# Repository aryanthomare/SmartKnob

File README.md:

<h1 align="center">SmartKnob</h1>

<p align="center">
  A programmable force-feedback knob for your computer. Custom motor-driver PCB, closed-loop haptic firmware,<br>
  a native Windows companion app and a parametric 3D-printed enclosure, all designed in house.
</p>

A brushless gimbal motor sits under the knob. By driving it with the right torque at every angle, the firmware makes
the same physical knob feel like a stepped volume dial, a smooth scroll wheel or a switch with hard end stops, and
changes that feel on the fly as you switch tasks on the PC. The knob talks to a small Windows tray app over USB or
Bluetooth LE, and works on its own as a media volume knob when the app isn't running.

## Contents

- [Features](#features)
- [System overview](#system-overview)
- [Hardware: the driver PCB](#hardware-the-driver-pcb)
- [Firmware](#firmware)
- [Desktop app](#desktop-app)
- [Enclosure](#enclosure)
- [How it was built](#how-it-was-built)
- [Building and flashing](#building-and-flashing)
- [Repository layout](#repository-layout)

## Features

- **Software-defined feel.** Detent strength, steps per degree and spring end stops are pushed from the PC per mode.
- **Exact volume, not key nudges.** With the app running, the knob sets system or per-app volume to the percent, and
  follows changes made elsewhere (keyboard, Windows mixer) so the dial never drifts.
- **Five modes:** system volume, volume of the focused app, scroll, zoom, and left/right arrow keys.
- **Wired or wireless.** USB-C, or Bluetooth LE from the 12 V barrel jack alone. The app switches between them
  automatically and prefers the cable.
- **Works without the app** as a USB or Bluetooth HID volume knob.
- **Liquid Glass style UI** rendered in software by a 280 KB native executable that uses no CPU while idle.

## System overview

```mermaid
flowchart LR
  subgraph Knob["Knob (ESP32-S3 firmware)"]
    ENC["AS5600 encoder<br/>12-bit, I²C"] --> CTRL["Control loop ~4.7 kHz<br/>FOC torque + haptic engine"]
    CTRL --> DRV["DRV8316 3-phase driver<br/>→ gimbal BLDC motor"]
    CTRL <--> PROTO["Line protocol<br/>HELLO · CFG · VAL · PING"]
    CTRL --> HID["HID volume keys<br/>(standalone)"]
  end
  PROTO <-- "USB CDC serial" --> APP
  PROTO <-- "BLE Nordic UART" --> APP
  HID -- "USB HID / HID-over-GATT" --> WIN["Windows"]
  subgraph PC["Windows PC"]
    APP["SmartKnob.exe<br/>tray app"] --> CA["Core Audio<br/>system + per-app volume"]
    APP --> SI["SendInput<br/>scroll · zoom · arrows"]
  end
```

The haptics always run on the knob, so the feel never waits on the PC. The app only sends a *haptic config* (range,
degrees per step, detent strength, wall stiffness) when the mode changes, and receives value changes back.

## Hardware: the driver PCB

A 54 × 54 mm, four-layer board designed in KiCad. The motor's axis sits at the board centre, the AS5600 encoder board
stacks above it on M3 standoffs, and the motor mounts on top of that.

| Block | Part | Notes |
|---|---|---|
| MCU | ESP32-S3-MINI-1-N8 | Native USB (no USB-UART bridge), BLE 5, 8 MB flash |
| Motor driver | TI DRV8316CR | 3-phase, integrated FETs, SPI config, 3× PWM mode, current-sense outputs |
| Encoder | AS5600 breakout | 12-bit magnetic angle over I²C, on its own board under the motor |
| Motor | 34.5 mm gimbal BLDC | 7 pole pairs (measured during bring-up) |
| 12 V input | DC barrel jack | P-MOSFET reverse-polarity block, 15 V gate clamp, SMAJ16A TVS |
| 5 V | TI TPS54202 buck | 12 V → 5.08 V, diode-ORed with USB VBUS |
| 3.3 V | AP2112K LDO | MCU, encoder and breakout header |
| USB-C | HRO TYPE-C-31-M-12 | 500 mA polyfuse, USBLC6 ESD protection |
| Misc | | JST-PH motor and encoder connectors, 2×5 breakout header, BOOT/RESET buttons, VM voltage sense |

```mermaid
flowchart LR
  J1["12 V barrel"] --> Q1["Reverse-polarity<br/>P-MOSFET + TVS"] --> VM["+12 V (VM)"]
  VM --> DRV["DRV8316<br/>motor supply"]
  VM --> BUCK["TPS54202 buck<br/>→ 5.08 V"] --> D4["Schottky"] --> V5["+5 V"]
  USB["USB-C VBUS"] --> F1["Polyfuse"] --> D3["Schottky"] --> V5
  V5 --> LDO["AP2112K"] --> V33["+3.3 V<br/>MCU · encoder"]
  VM --> SENSE["÷11 divider → GPIO7<br/>(VM sense)"]
```

The two 5 V sources are diode-ORed, so the logic runs from either USB or the barrel jack. Motor power only comes
from the barrel jack, so on USB alone the knob still reads the encoder and talks to the PC, and the firmware turns
haptics off until 12 V is present.

**Layer stack.** Signals on the outer layers, a solid ground plane on inner 1 under everything, and inner 2 split
between the 12 V motor supply and 3.3 V. The DRV8316's thermal pad drops straight into the ground plane through a via
array, and the ESP32 antenna overhangs a copper keep-out.

<details>
<summary><b>Schematic sheets</b> (hierarchical: power, driver, MCU, connectors)</summary>

The design notes on each sheet record the datasheet decisions: feedback divider values, which DRV8316 pins may not
float, strapping pins to avoid, ADC1-only analog inputs because ADC2 is unusable with the radio on, and so on.

**Power**

**Motor driver**

**MCU**

**Connectors**

Full PDF: [hardware/smartknob_driver/smartknob_driver_schematic.pdf](hardware/smartknob_driver/smartknob_driver_schematic.pdf)
</details>

**Fabrication.** [`hardware/smartknob_driver/fab`](hardware/smartknob_driver/fab) has Gerbers, drill files and a
JLCPCB assembly BOM and placement file with LCSC part numbers, so the board can be ordered fully assembled.

## Firmware

[`volume_knob/src/main.cpp`](volume_knob/src/main.cpp) · Arduino on ESP32-S3 via PlatformIO

**Motor control.** At power-up the firmware calibrates itself: it aligns the rotor with a fixed voltage vector to find
the encoder direction and the electrical zero, then applies a test push to learn the torque sign. After that it runs
voltage-mode field-oriented control: every loop it reads the encoder over 400 kHz I²C, computes the electrical angle,
and puts the requested torque on the q-axis through 20 kHz PWM. The loop runs at about 4.7 kHz. Drive voltage is
capped per supply (3 V on 12 V, 1.2 V when VM is low), and a DRV8316 fault or loss of motor power drops the knob
into plain-encoder mode instead of driving blind.

**Haptic engine.** The knob tracks an integer value in `[lo, hi]` with one value every `step` degrees. Around each
value a capped spring pulls the knob to the detent centre, and past either end a stiffer spring wall pushes it back,
with damping on both. Hysteresis on the step boundary stops the value chattering.

<p align="center">
  <picture>
    <source media="(prefers-color-scheme: dark)" srcset="docs/images/haptic_profile_dark.png">
    
  </picture>
</p>

**Two ways to run.**

- *Host mode:* the app sends a haptic config per mode and the knob streams value changes back.
- *Standalone:* with no app for 3 s, the knob becomes a media-key volume knob. HID can only nudge the volume, so on
  connect it drives Windows to 0 % and back up to a known level, unless the app reported the real level shortly before
  it went away.

**Protocol.** Plain text lines, identical over USB serial and Bluetooth:

| Direction | Message | Meaning |
|---|---|---|
| PC → knob | `HELLO` | Handshake, answered with `INFO name=SmartKnob fw=2 hap=<0/1>` |
| PC → knob | `CFG lo= hi= val= step= det= wall=` | Range, current value, degrees per step, detent volts, wall stiffness |
| PC → knob | `VAL v=` | Move the value without moving the knob (volume changed elsewhere) |
| PC → knob | `PING vol=` | Keep-alive (3 s timeout) plus the PC's real volume, answered with `PONG hap= vm=` |
| knob → PC | `VAL v=` | The user turned the knob |

**Connectivity.** USB enumerates as a composite device (HID consumer control + CDC serial) with its own product ID.
Over Bluetooth LE the knob exposes two services on one connection: HID-over-GATT for the standalone volume keys and
the Nordic UART Service for the protocol. Every message the firmware prints goes to both transports.

## Desktop app

[`desktop/smartknob.cpp`](desktop/smartknob.cpp) · C++17, Win32, GDI+, C++/WinRT

<table>
  <tr>
    <td></td>
    <td></td>
  </tr>
  <tr>
    <td colspan="2" align="center"><br><sub>Volume popup shown while turning</sub></td>
  </tr>
</table>

A tray app with a floating panel for picking the mode and click strength, and a volume popup that appears while you
turn the knob.

- **Volume:** sets the Windows master volume exactly through Core Audio (`IAudioEndpointVolume`), and listens for
  changes made elsewhere so the knob's haptic position stays in sync. It tags its own writes so it can ignore them.
- **App volume:** follows the foreground window (`SetWinEventHook`) and adjusts every audio session of that process.
- **Scroll / Zoom / Arrow keys:** relative modes that emit wheel events, Ctrl+wheel or ←/→ through `SendInput`, each
  with its own detent feel.
- **Connection:** finds the knob by USB ID and opens it with overlapped I/O on a reader thread. If there's no cable it
  connects to the paired knob's GATT service with C++/WinRT on a worker thread, and moves to USB as soon as a cable
  appears. The UI thread never blocks on either.

**Liquid Glass material, in software.** The panel and popup follow Apple's Liquid Glass guidelines without any GPU
framework:

- The screen behind the window is captured, downsampled, saturated and box-blurred. The windows exclude themselves from
  capture, so they never see their own pixels.
- Each pixel then gets a lens offset from the shape's signed distance field, so content bends at the rim, with slight
  chromatic dispersion, a specular rim lit from the top left, an adaptive tint and a soft shadow.
- The small popup flips light or dark with the luminance behind it, and corners are concentric (inner radius = outer
  radius − padding).
- It honours Windows dark mode, transparency effects, animation settings and high contrast.
- It only re-captures while a window is visible, and only re-renders when what's behind it changed: about 1 % of
  one core with the panel open, nothing when hidden.

**Footprint:** one 280 KB statically linked executable, no runtime to install, about 7 MB of memory, 0 % CPU idle.
Settings live in `%APPDATA%\SmartKnob\settings.ini`.

## Enclosure

[`enclosure/smartknob_enclosure.fs`](enclosure/smartknob_enclosure.fs) · Onshape FeatureScript

The whole enclosure is a single code-defined Onshape feature, so changing a standoff height or the knob fit is one
constant and a rebuild.

- **Cover:** one printed piece. A side profile (flat deck over the motor, rounded slope down to a low nose on the
  cable side) is intersected with the plan shape, filleted along the top and shelled from the open bottom. It has
  cut-outs for the motor, barrel jack, USB-C plug and paper-clip access to BOOT/RESET.
- **Base plate:** a locating lip, and counterbored M3 holes on the board's 24 mm mounting square.
- **Encoder spacers:** printed rings that lift the AS5600 board clear of the barrel jack.
- **Knob cap:** 40 mm, 40 grip flutes and a pointer dimple. Four pegs press-fit into the rotor's M2.5 holes, with peg
  diameter as a printer-tuning constant.
- **Reference stack:** the populated PCB (built from the KiCad 3D models' bounding boxes, in the same coordinate frame
  as the KiCad STEP export), the encoder board, standoffs and motor.
- **Self-checks:** the feature measures the distance between the enclosure and everything inside it, warns on
  interference and reports the minimum clearance.

## How it was built

The whole stack was designed in house and brought up one layer at a time.

1. **Board design.** A hierarchical schematic in KiCad with datasheet decisions written onto each sheet, then a
   four-layer layout around a centred motor axis, with the JST connectors on the cable side and the power entry on
   the opposite edge. Exported Gerbers, drill files and a JLCPCB assembly BOM and placement file.
2. **Encoder bring-up.** [`encoder_test`](encoder_test/src/main.cpp) scans the I²C bus and streams raw angle,
   magnet status and AGC to confirm the magnet height.
3. **Motor bring-up.** [`motor_test`](motor_test/src/main.cpp) brings up the DRV8316 over SPI and checks supply and
   faults. It steps through the phases while watching the rotor, sweeps electrical revolutions to measure the pole
   pairs (7), and spins the motor open-loop in both directions before any closed-loop code runs.
4. **Enclosure.** Iterated in Onshape around a STEP export of the real board. Parameters live as constants rather
   than feature-dialog inputs, so pushing new code never invalidates the feature.
5. **Firmware.** Closed-loop FOC and the generic haptic engine, first as a standalone USB volume knob, then with the
   host protocol.
6. **Desktop app.** First prototyped in Python, then rewritten as a native Win32 executable to keep the memory and
   CPU footprint negligible.
7. **Bluetooth.** Added as a second transport carrying the same protocol, so the knob runs from the barrel jack alone.

**Problems found on real hardware**

- **Port mix-up.** The knob first enumerated with Espressif's default USB product ID, the same one as the chip's
  built-in flashing port, which the app deliberately never opens. The firmware now sets its own PID. Because the
  Arduino core starts USB before `setup()` when CDC-on-boot is enabled, that meant turning CDC-on-boot off and owning
  the serial object.
- **Buzzing at the end stops.** After the knob was released past 0 % or 100 %, the wall spring returned it to rest
  about 1° past the end, where friction holds it. There the wall's damping term was amplifying one-LSB encoder
  jitter, which differentiates to tens of degrees per second, into ±0.25 V of noise. That was three times the spring
  force, so the motor sat buzzing between −0.32 V and +0.17 V. A heavier velocity filter plus a 30 °/s deadband on
  the damping fixed it: the motor now holds a steady −0.07 V. A test command that shifts the knob's reference point
  made the bug reproducible on the bench without touching the knob.

## Building and flashing

**Firmware** (PlatformIO):

```sh
cd volume_knob
pio run -t upload        # first flash goes through the chip's USB-Serial/JTAG port (COM3 in platformio.ini)
```

Once the firmware is running, the board shows up as `303A:4B4E` (HID + serial) and the flashing port disappears. To
reflash, choose **Disconnect for firmware update** in the app's tray menu, then open the knob's COM port at 1200 baud
to reboot into the bootloader. Holding BOOT while plugging in also works.

**Desktop app** (Visual Studio with the C++ workload):

```bat
desktop\build.bat
desktop\SmartKnob.exe
```

`SmartKnob.exe --snapshot <dir>` renders the panel and popup over the current screen to PNGs and exits. The UI images
in this README were made that way.

**Bluetooth:** pair "SmartKnob" once in Windows Settings → Bluetooth. Windows caches the knob's services, so after
changing them in firmware, remove the device and pair again.

## Repository layout

```
hardware/smartknob_driver/   KiCad project: schematic, 4-layer PCB, custom symbols/footprints, fab outputs
volume_knob/                 Main firmware: FOC, haptic engine, USB + BLE protocol, HID
encoder_test/                Bring-up: AS5600 over I²C
motor_test/                  Bring-up: DRV8316 + open-loop motor tests
desktop/                     Windows companion app (single C++ file + build script)
enclosure/                   Onshape FeatureScript enclosure + board STEP export
docs/images/                 README images (renders, schematic sheets, app snapshots)
```

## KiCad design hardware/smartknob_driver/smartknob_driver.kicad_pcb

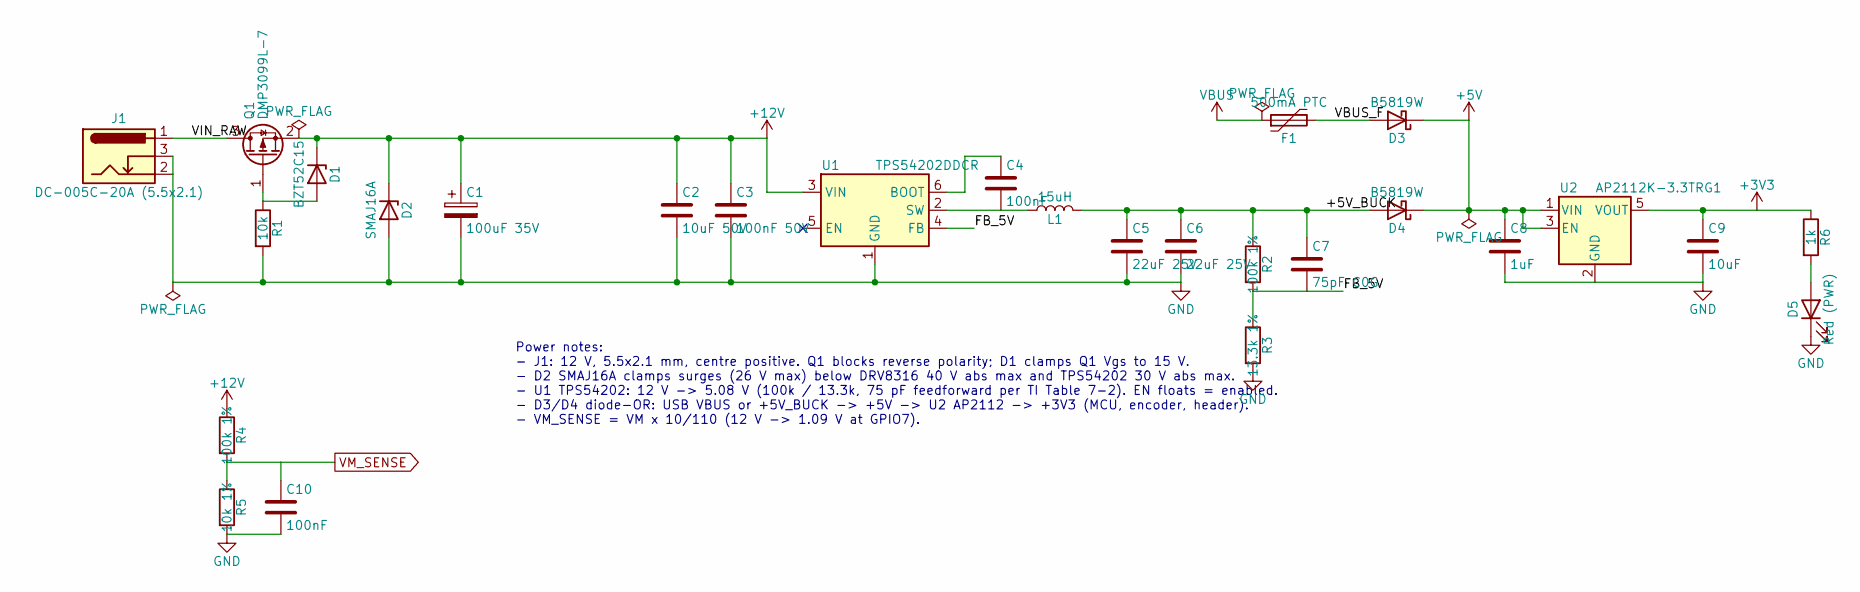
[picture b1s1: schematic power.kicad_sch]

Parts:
C1: 100uF 35V; CP_Elec_6.3x7.7; LCSC C294520
C2: 10uF 50V; C_1206_3216Metric; LCSC C13585
C3: 100nF 50V; C_0603_1608Metric; LCSC C14663
C4, C10: 100nF; C_0402_1005Metric; LCSC C1525
C5, C6: 22uF 25V; C_0805_2012Metric; LCSC C45783
C7: 75pF C0G; C_0402_1005Metric; LCSC C107010
C8: 1uF; C_0402_1005Metric; LCSC C52923
C9: 10uF; C_0603_1608Metric; LCSC C19702
D1: BZT52C15; D_SOD-123; LCSC C2932746
D2: SMAJ16A; D_SMA; LCSC C74561
D3, D4: B5819W; D_SOD-123; LCSC C8598
D5: Red (PWR); LED_0603_1608Metric; LCSC C2286
F1: 500mA PTC; Fuse_0805_2012Metric; LCSC C20978
J1: DC-005C-20A (5.5x2.1); BarrelJack_Hroparts_DC-005C-20A_Horizontal; LCSC C84007
L1: 15uH; L_Sunlord_SWPA5040S; LCSC C44888
Q1: DMP3099L-7; SOT-23; LCSC C155244
R1: 10k; R_0402_1005Metric; LCSC C25744
R2, R4: 100k 1%; R_0402_1005Metric; LCSC C25741
R3: 13.3k 1%; R_0402_1005Metric; LCSC C274352
R5: 10k 1%; R_0402_1005Metric; LCSC C25744
R6: 1k; R_0402_1005Metric; LCSC C11702
U1: TPS54202DDCR; SOT-23-6; LCSC C191884
U2: AP2112K-3.3TRG1; SOT-23-5; LCSC C51118

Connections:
+3V3: C9.1, R6.1, U2.5 (VOUT); also elsewhere on the board
+5V: C8.1, D3.1 (K), D4.1 (K), U2.1 (VIN), U2.3 (EN)
+12V: C1.1, C2.1, C3.1, D1.1 (K), D2.1 (K), Q1.2 (S), R4.1, U1.3 (VIN); also elsewhere on the board
/Power/+5V_BUCK: C5.1, C6.1, C7.1, D4.2 (A), L1.2, R2.1
/Power/FB_5V: C7.2, R2.2, R3.1, U1.4 (FB)
/Power/VBUS_F: D3.2 (A), F1.2
/Power/VIN_RAW: J1.1, Q1.3 (D)
GND: C1.2, C2.2, C3.2, C5.2, C6.2, C8.2, C9.2, C10.2, D2.2 (A), D5.1 (K), J1.2, J1.3, R1.2, R3.2, R5.2, U1.1 (GND), U2.2 (GND); also elsewhere on the board
unnamed: D1.2 (A), Q1.1 (G), R1.1
unnamed: D5.2 (A), R6.2
unnamed: C4.1, U1.6 (BOOT)
unnamed: C4.2, L1.1, U1.2 (SW)
VBUS: F1.1; also elsewhere on the board
VM_SENSE: C10.1, R4.2, R5.1; also elsewhere on the board

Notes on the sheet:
Power notes: - J1: 12 V, 5.5x2.1 mm, centre positive. Q1 blocks reverse polarity; D1 clamps Q1 Vgs to 15 V. - D2 SMAJ16A clamps surges (26 V max) below DRV8316 40 V abs max and TPS54202 30 V abs max. - U1 TPS54202: 12 V -> 5.08 V (100k / 13.3k, 75 pF feedforward per TI Table 7-2). EN floats = enabl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

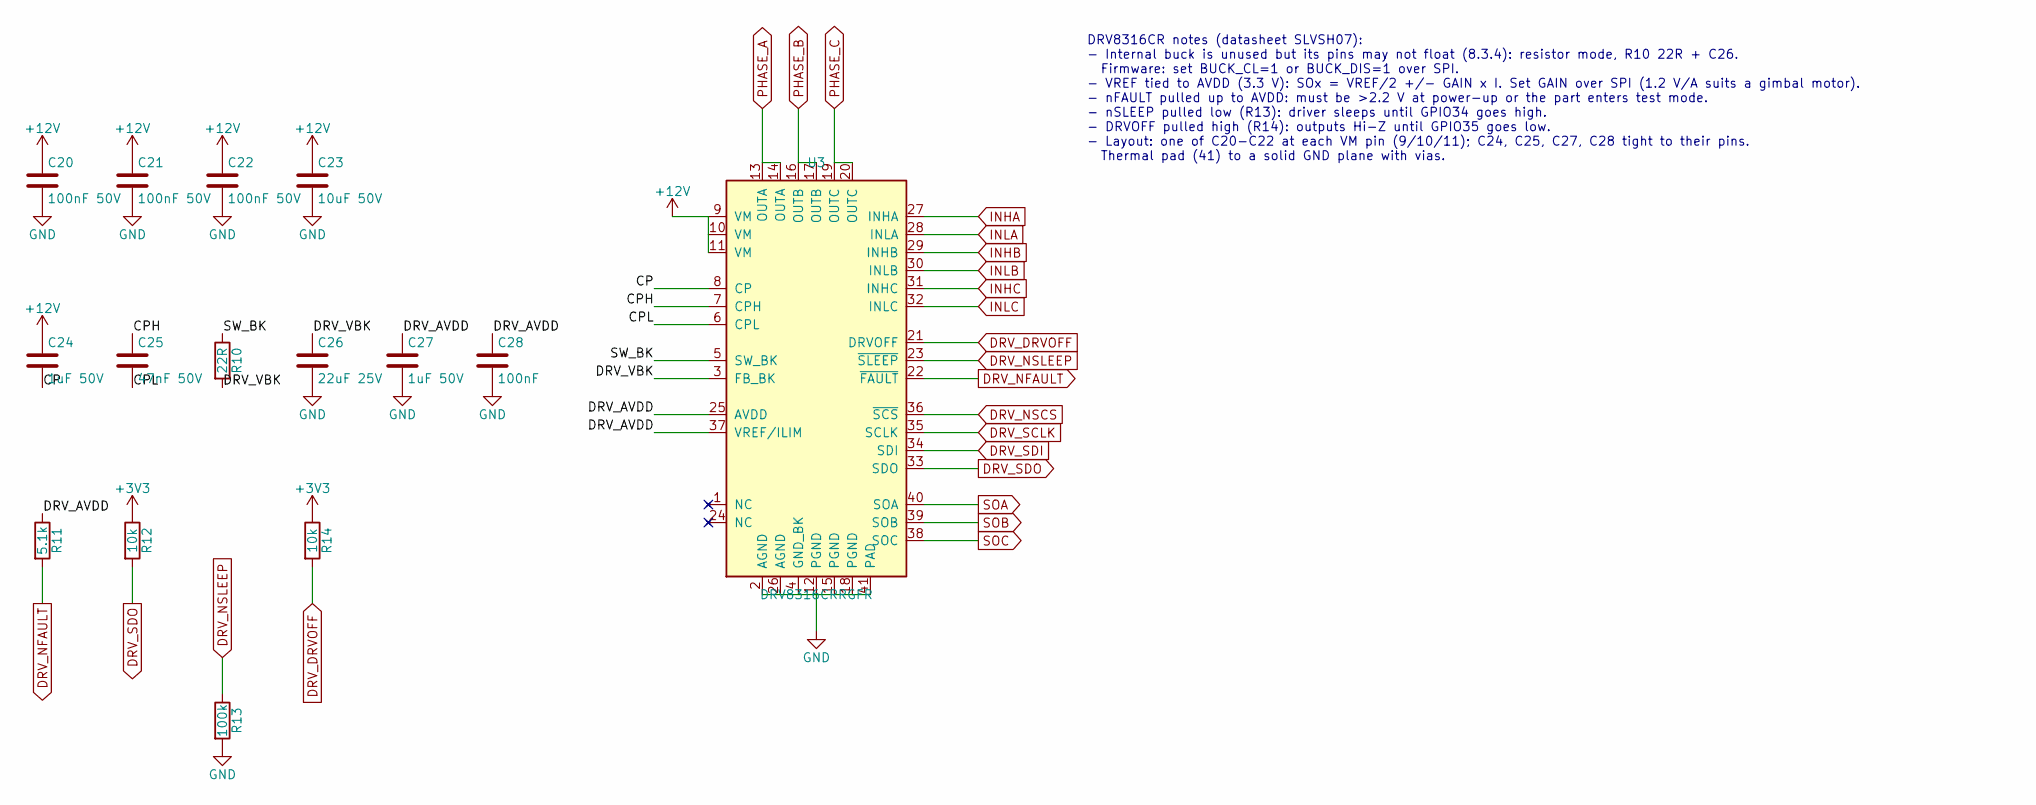
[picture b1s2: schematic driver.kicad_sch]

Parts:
C20, C21, C22: 100nF 50V; C_0603_1608Metric; LCSC C14663
C23: 10uF 50V; C_1206_3216Metric; LCSC C13585
C24, C27: 1uF 50V; C_0603_1608Metric; LCSC C15849
C25: 47nF 50V; C_0603_1608Metric; LCSC C1622
C26: 22uF 25V; C_0805_2012Metric; LCSC C45783
C28: 100nF; C_0402_1005Metric; LCSC C1525
R10: 22R; R_0603_1608Metric; LCSC C23345
R11: 5.1k; R_0402_1005Metric; LCSC C25905
R12, R14: 10k; R_0402_1005Metric; LCSC C25744
R13: 100k; R_0402_1005Metric; LCSC C25741
U3: DRV8316CRRGFR; TI_RGF0040E_VQFN-40-1EP_5x7mm_P0.5mm_EP3.7x5.7mm_ThermalVias; LCSC C5447274

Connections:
+3V3: R12.1, R14.1; also elsewhere on the board
+12V: C20.1, C21.1, C22.1, C23.1, C24.1, U3.9 (VM), U3.10 (VM), U3.11 (VM); also elsewhere on the board
/Driver/CP: C24.2, U3.8 (CP)
/Driver/CPH: C25.1, U3.7 (CPH)
/Driver/CPL: C25.2, U3.6 (CPL)
/Driver/DRV_AVDD: C27.1, C28.1, R11.1, U3.25 (AVDD), U3.37 (VREF/ILIM)
/Driver/DRV_VBK: C26.1, R10.2, U3.3 (FB_BK)
/Driver/SW_BK: R10.1, U3.5 (SW_BK)
DRV_DRVOFF: R14.2, U3.21 (DRVOFF); also elsewhere on the board
DRV_NFAULT: R11.2, U3.22 (~FAULT); also elsewhere on the board
DRV_NSCS: U3.36 (~SCS); also elsewhere on the board
DRV_NSLEEP: R13.1, U3.23 (~SLEEP); also elsewhere on the board
DRV_SCLK: U3.35 (SCLK); also elsewhere on the board
DRV_SDI: U3.34 (SDI); also elsewhere on the board
DRV_SDO: R12.2, U3.33 (SDO); also elsewhere on the board
GND: C20.2, C21.2, C22.2, C23.2, C26.2, C27.2, C28.2, R13.2, U3.2 (AGND), U3.4 (GND_BK), U3.12 (PGND), U3.15 (PGND), U3.18 (PGND), U3.26 (AGND), U3.41 (PAD); also elsewhere on the board
INHA: U3.27 (INHA); also elsewhere on the board
INHB: U3.29 (INHB); also elsewhere on the board
INHC: U3.31 (INHC); also elsewhere on the board
INLA: U3.28 (INLA); also elsewhere on the board
INLB: U3.30 (INLB); also elsewhere on the board
INLC: U3.32 (INLC); also elsewhere on the board
PHASE_A: U3.13 (OUTA), U3.14 (OUTA); also elsewhere on the board
PHASE_B: U3.16 (OUTB), U3.17 (OUTB); also elsewhere on the board
PHASE_C: U3.19 (OUTC), U3.20 (OUTC); also elsewhere on the board
SOA: U3.40 (SOA); also elsewhere on the board
SOB: U3.39 (SOB); also elsewhere on the board
SOC: U3.38 (SOC); also elsewhere on the board

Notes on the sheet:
DRV8316CR notes (datasheet SLVSH07): - Internal buck is unused but its pins may not float (8.3.4): resistor mode, R10 22R + C26. Firmware: set BUCK_CL=1 or BUCK_DIS=1 over SPI. - VREF tied to AVDD (3.3 V): SOx = VREF/2 +/- GAIN x I. Set GAIN over SPI (1.2 V/A suits a gimbal motor). - nFAULT pulled 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

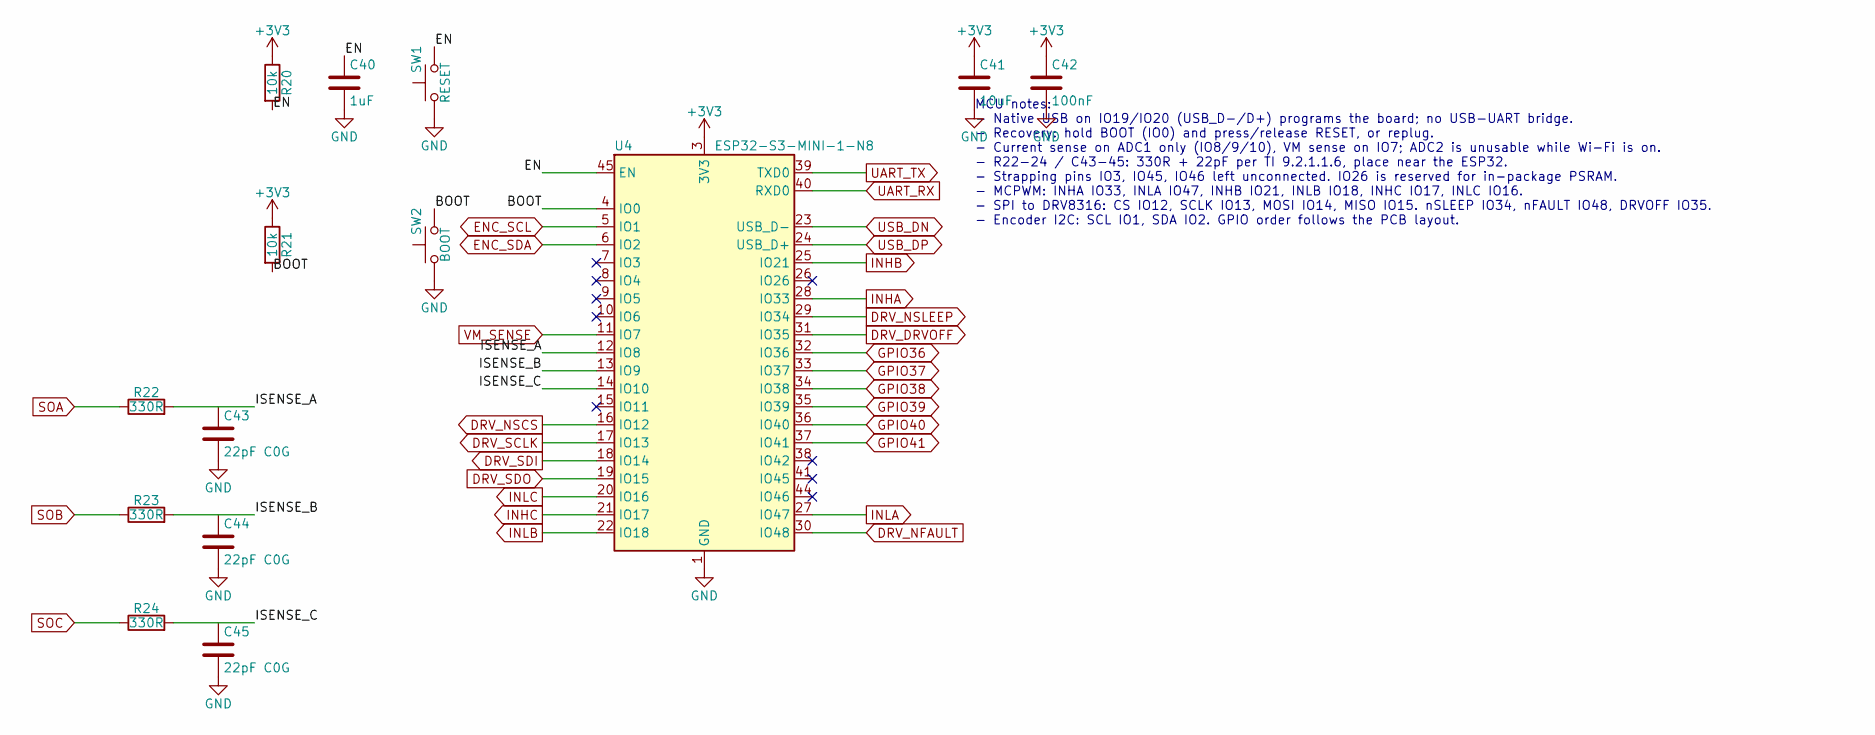
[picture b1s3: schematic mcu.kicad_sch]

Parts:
C40: 1uF; C_0402_1005Metric; LCSC C52923
C41: 10uF; C_0603_1608Metric; LCSC C19702
C42: 100nF; C_0402_1005Metric; LCSC C1525
C43, C44, C45: 22pF C0G; C_0402_1005Metric; LCSC C1555
R20, R21: 10k; R_0402_1005Metric; LCSC C25744
R22, R23, R24: 330R; R_0402_1005Metric; LCSC C25104
SW1: RESET; SW_Push_1P1T_XKB_TS-1187A; LCSC C318884
SW2: BOOT; SW_Push_1P1T_XKB_TS-1187A; LCSC C318884
U4: ESP32-S3-MINI-1-N8; ESP32-S2-MINI-1; LCSC C2913206

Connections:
+3V3: C41.1, C42.1, R20.1, R21.1, U4.3 (3V3); also elsewhere on the board
/MCU/BOOT: R21.2, SW2.2, U4.4 (IO0)
/MCU/EN: C40.1, R20.2, SW1.2, U4.45 (EN)
/MCU/ISENSE_A: C43.1, R22.2, U4.12 (IO8)
/MCU/ISENSE_B: C44.1, R23.2, U4.13 (IO9)
/MCU/ISENSE_C: C45.1, R24.2, U4.14 (IO10)
DRV_DRVOFF: U4.31 (IO35); also elsewhere on the board
DRV_NFAULT: U4.30 (IO48); also elsewhere on the board
DRV_NSCS: U4.16 (IO12); also elsewhere on the board
DRV_NSLEEP: U4.29 (IO34); also elsewhere on the board
DRV_SCLK: U4.17 (IO13); also elsewhere on the board
DRV_SDI: U4.18 (IO14); also elsewhere on the board
DRV_SDO: U4.19 (IO15); also elsewhere on the board
ENC_SCL: U4.5 (IO1); also elsewhere on the board
ENC_SDA: U4.6 (IO2); also elsewhere on the board
GND: C40.2, C41.2, C42.2, C43.2, C44.2, C45.2, SW1.1, SW2.1, U4.1 (GND), U4.2 (GND), U4.42 (GND), U4.43 (GND), U4.46 (GND), U4.47 (GND), U4.48 (GND), U4.49 (GND), U4.50 (GND), U4.51 (GND), U4.52 (GND), U4.53 (GND), U4.54 (GND), U4.55 (GND), U4.56 (GND), U4.57 (GND), U4.58 (GND), U4.59 (GND), U4.60 (GND), U4.61 (GND), U4.62 (GND), U4.63 (GND), U4.64 (GND), U4.65 (GND); also elsewhere on the board
GPIO36: U4.32 (IO36); also elsewhere on the board
GPIO37: U4.33 (IO37); also elsewhere on the board
GPIO38: U4.34 (IO38); also elsewhere on the board
GPIO39: U4.35 (IO39); also elsewhere on the board
GPIO40: U4.36 (IO40); also elsewhere on the board
GPIO41: U4.37 (IO41); also elsewhere on the board
INHA: U4.28 (IO33); also elsewhere on the board
INHB: U4.25 (IO21); also elsewhere on the board
INHC: U4.21 (IO17); also elsewhere on the board
INLA: U4.27 (IO47); also elsewhere on the board
INLB: U4.22 (IO18); also elsewhere on the board
INLC: U4.20 (IO16); also elsewhere on the board
SOA: R22.1; also elsewhere on the board
SOB: R23.1; also elsewhere on the board
SOC: R24.1; also elsewhere on the board
UART_RX: U4.40 (RXD0); also elsewhere on the board
UART_TX: U4.39 (TXD0); also elsewhere on the board
USB_DN: U4.23 (USB_D-); also elsewhere on the board
USB_DP: U4.24 (USB_D+); also elsewhere on the board
VM_SENSE: U4.11 (IO7); also elsewhere on the board

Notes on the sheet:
MCU notes: - Native USB on IO19/IO20 (USB_D-/D+) programs the board; no USB-UART bridge. - Recovery: hold BOOT (IO0) and press/release RESET, or replug. - Current sense on ADC1 only (IO8/9/10), VM sense on IO7; ADC2 is unusable while Wi-Fi is on. - R22-24 / C43-45: 330R + 22pF per TI 9.2.1.1.6, pla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

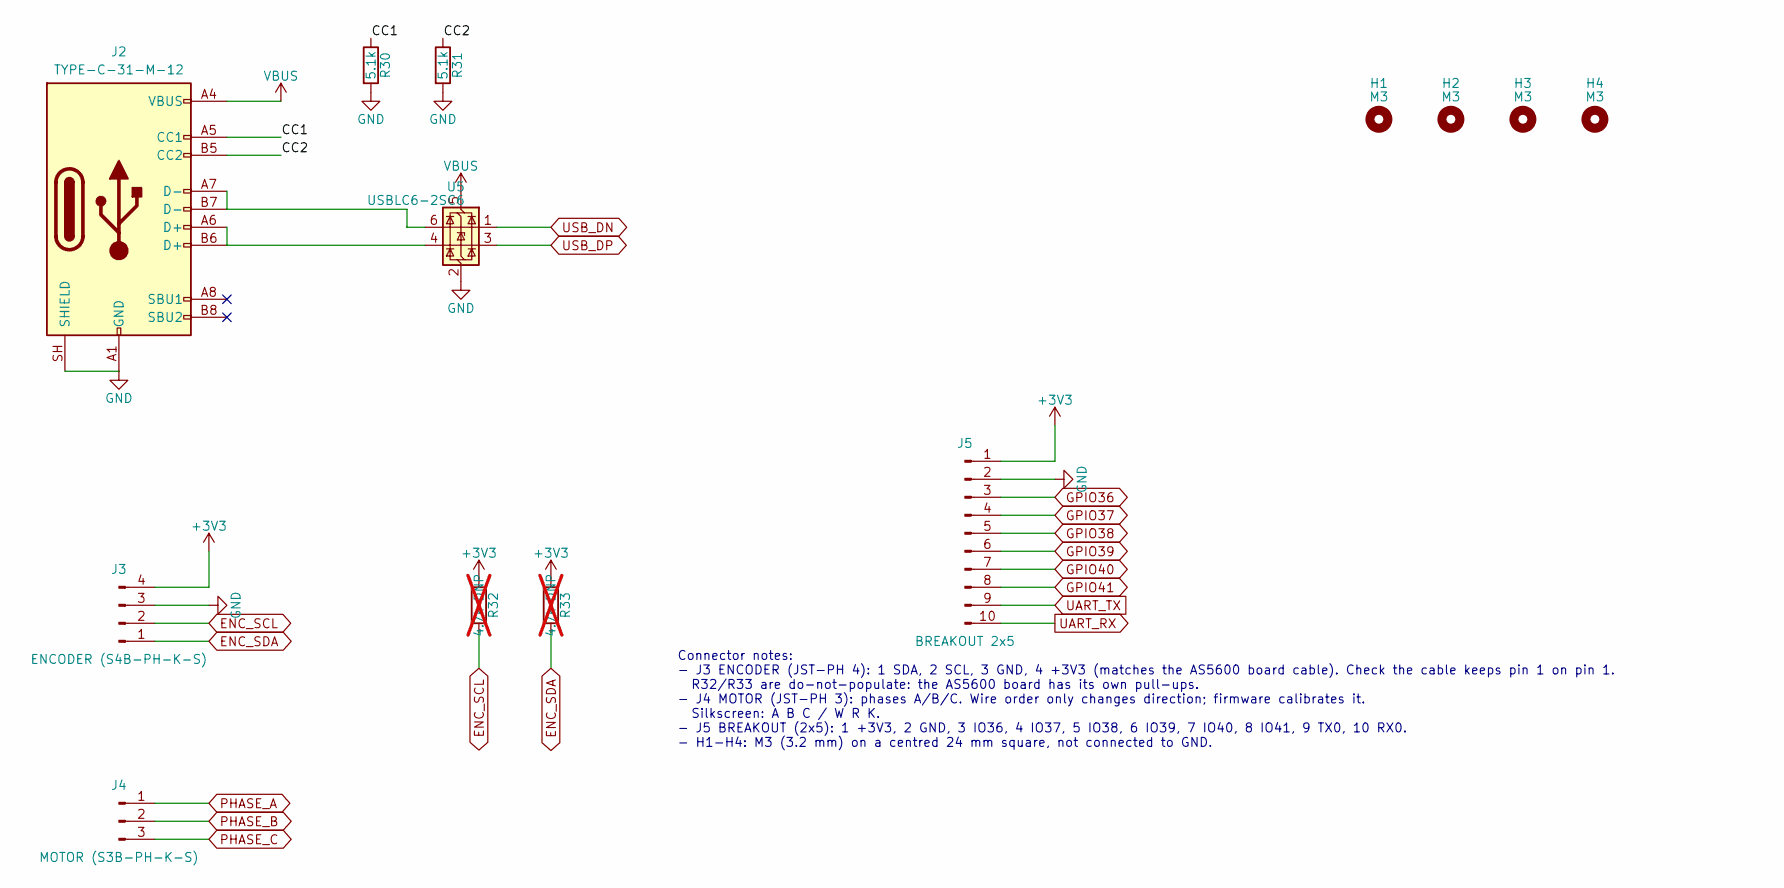
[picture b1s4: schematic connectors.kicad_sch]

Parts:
H1, H2, H3, H4: M3; MountingHole_3.2mm_M3
J2: TYPE-C-31-M-12; USB_C_Receptacle_HRO_TYPE-C-31-M-12; LCSC C165948
J3: ENCODER (S4B-PH-K-S); JST_PH_S4B-PH-K_1x04_P2.00mm_Horizontal; LCSC C157926
J4: MOTOR (S3B-PH-K-S); JST_PH_S3B-PH-K_1x03_P2.00mm_Horizontal; LCSC C157929
J5: BREAKOUT 2x5; PinHeader_2x05_P2.54mm_Vertical
R30, R31: 5.1k; R_0402_1005Metric; LCSC C25905
R32, R33: 4.7k DNP; R_0402_1005Metric; LCSC C25900; not fitted
U5: USBLC6-2SC6; SOT-23-6; LCSC C7519

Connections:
+3V3: J3.4, J5.1, R32.1, R33.1; also elsewhere on the board
/Connectors/CC1: J2.A5 (CC1), R30.1
/Connectors/CC2: J2.B5 (CC2), R31.1
ENC_SCL: J3.2, R32.2; also elsewhere on the board
ENC_SDA: J3.1, R33.2; also elsewhere on the board
GND: J2.A1 (GND), J2.A12 (GND), J2.B1 (GND), J2.B12 (GND), J2.SH (SHIELD), J3.3, J5.2, R30.2, R31.2, U5.2 (GND); also elsewhere on the board
GPIO36: J5.3; also elsewhere on the board
GPIO37: J5.4; also elsewhere on the board
GPIO38: J5.5; also elsewhere on the board
GPIO39: J5.6; also elsewhere on the board
GPIO40: J5.7; also elsewhere on the board
GPIO41: J5.8; also elsewhere on the board
unnamed: J2.A6 (D+), J2.B6 (D+), U5.4 (I/O2)
unnamed: J2.A7 (D-), J2.B7 (D-), U5.6 (I/O1)
PHASE_A: J4.1; also elsewhere on the board
PHASE_B: J4.2; also elsewhere on the board
PHASE_C: J4.3; also elsewhere on the board
UART_RX: J5.10; also elsewhere on the board
UART_TX: J5.9; also elsewhere on the board
USB_DN: U5.1 (I/O1); also elsewhere on the board
USB_DP: U5.3 (I/O2); also elsewhere on the board
VBUS: J2.A4 (VBUS), J2.A9 (VBUS), J2.B4 (VBUS), J2.B9 (VBUS), U5.5 (VBUS); also elsewhere on the board

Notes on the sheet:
Connector notes: - J3 ENCODER (JST-PH 4): 1 SDA, 2 SCL, 3 GND, 4 +3V3 (matches the AS5600 board cable). Check the cable keeps pin 1 on pin 1. R32/R33 are do-not-populate: the AS5600 board has its own pull-ups. - J4 MOTOR (JST-PH 3): phases A/B/C. Wire order only changes direction; firmware calibrat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

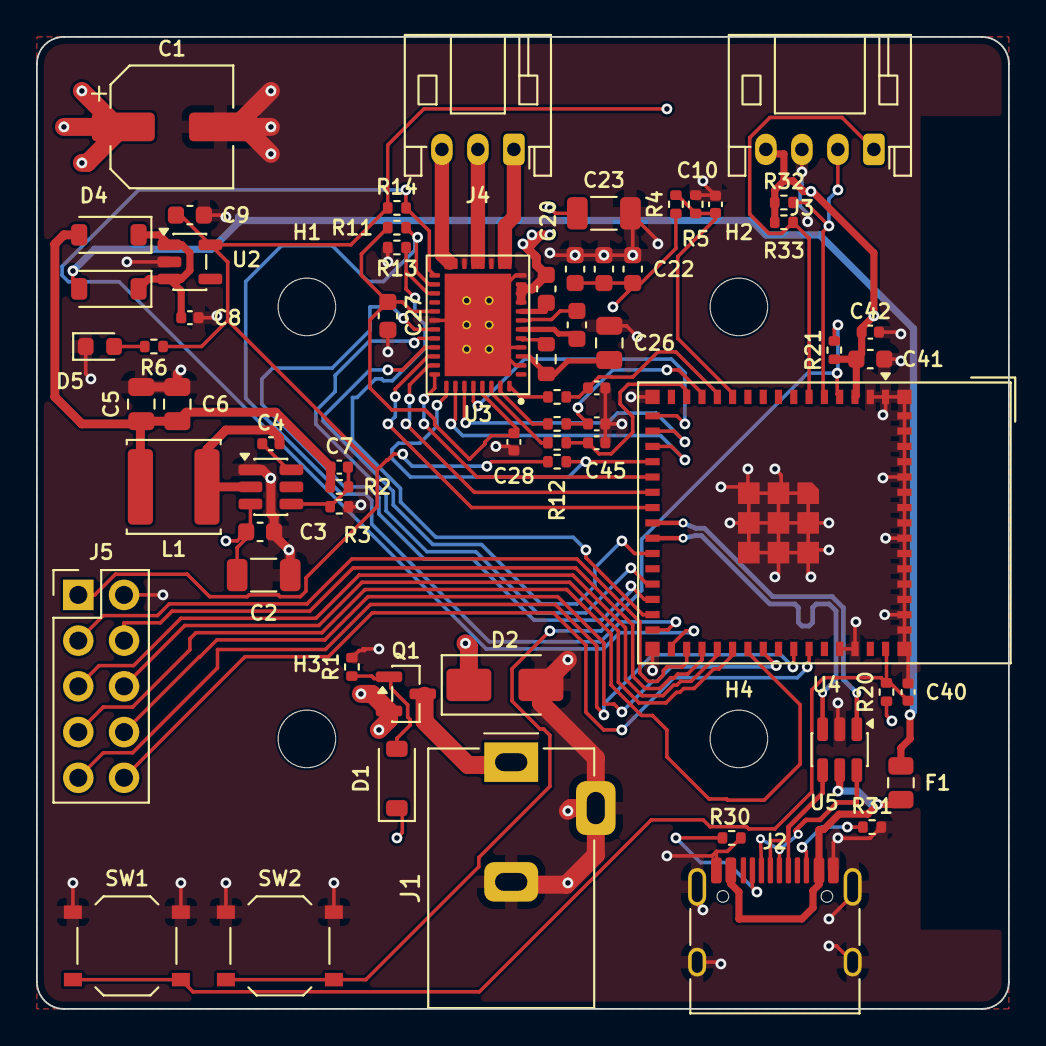
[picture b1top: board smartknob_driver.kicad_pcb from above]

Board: 4 copper layers, 54.0 x 54.0 mm, 69 parts (0 on the bottom side), 60 nets.

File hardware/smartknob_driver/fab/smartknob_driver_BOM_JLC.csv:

"Comment","Designator","Footprint","LCSC Part #","Quantity"
"100uF 35V","C1","Capacitor_SMD:CP_Elec_6.3x7.7","C294520","1"
"10uF 50V","C2,C23","Capacitor_SMD:C_1206_3216Metric","C13585","2"
"100nF 50V","C3,C20,C21,C22","Capacitor_SMD:C_0603_1608Metric","C14663","4"
"100nF","C4,C10,C28,C42","Capacitor_SMD:C_0402_1005Metric","C1525","4"
"22uF 25V","C5,C6,C26","Capacitor_SMD:C_0805_2012Metric","C45783","3"
"75pF C0G","C7","Capacitor_SMD:C_0402_1005Metric","C107010","1"
"1uF","C8,C40","Capacitor_SMD:C_0402_1005Metric","C52923","2"
"10uF","C9,C41","Capacitor_SMD:C_0603_1608Metric","C19702","2"
"1uF 50V","C24,C27","Capacitor_SMD:C_0603_1608Metric","C15849","2"
"47nF 50V","C25","Capacitor_SMD:C_0603_1608Metric","C1622","1"
"22pF C0G","C43,C44,C45","Capacitor_SMD:C_0402_1005Metric","C1555","3"
"BZT52C15","D1","Diode_SMD:D_SOD-123","C2932746","1"
"SMAJ16A","D2","Diode_SMD:D_SMA","C74561","1"
"B5819W","D3,D4","Diode_SMD:D_SOD-123","C8598","2"
"Red (PWR)","D5","LED_SMD:LED_0603_1608Metric","C2286","1"
"500mA PTC","F1","Fuse:Fuse_0805_2012Metric","C20978","1"
"DC-005C-20A (5.5x2.1)","J1","smartknob:BarrelJack_Hroparts_DC-005C-20A_Horizontal","C84007","1"
"TYPE-C-31-M-12","J2","Connector_USB:USB_C_Receptacle_HRO_TYPE-C-31-M-12","C165948","1"
"ENCODER (S4B-PH-K-S)","J3","Connector_JST:JST_PH_S4B-PH-K_1x04_P2.00mm_Horizontal","C157926","1"
"MOTOR (S3B-PH-K-S)","J4","Connector_JST:JST_PH_S3B-PH-K_1x03_P2.00mm_Horizontal","C157929","1"
"BREAKOUT 2x5","J5","Connector_PinHeader_2.54mm:PinHeader_2x05_P2.54mm_Vertical","","1"
"15uH","L1","Inductor_SMD:L_Sunlord_SWPA5040S","C44888","1"
"DMP3099L-7","Q1","Package_TO_SOT_SMD:SOT-23","C155244","1"
"10k 1%","R1,R5,R12,R14,R20,R21","Resistor_SMD:R_0402_1005Metric","C25744","6"
"100k 1%","R2,R4,R13","Resistor_SMD:R_0402_1005Metric","C25741","3"
"13.3k 1%","R3","Resistor_SMD:R_0402_1005Metric","C274352","1"
"1k","R6","Resistor_SMD:R_0402_1005Metric","C11702","1"
"22R","R10","Resistor_SMD:R_0603_1608Metric","C23345","1"
"5.1k","R11,R30,R31","Resistor_SMD:R_0402_1005Metric","C25905","3"
"330R","R22,R23,R24","Resistor_SMD:R_0402_1005Metric","C25104","3"
"TS-1187A pushbutton","SW1,SW2","Button_Switch_SMD:SW_Push_1P1T_XKB_TS-1187A","C318884","2"
"TPS54202DDCR","U1","Package_TO_SOT_SMD:SOT-23-6","C191884","1"
"AP2112K-3.3TRG1","U2","Package_TO_SOT_SMD:SOT-23-5","C51118","1"
"DRV8316CRRGFR","U3","smartknob:TI_RGF0040E_VQFN-40-1EP_5x7mm_P0.5mm_EP3.7x5.7mm_ThermalVias","C5447274","1"
"ESP32-S3-MINI-1-N8","U4","RF_Module:ESP32-S2-MINI-1","C2913206","1"
"USBLC6-2SC6","U5","Package_TO_SOT_SMD:SOT-23-6","C7519","1"

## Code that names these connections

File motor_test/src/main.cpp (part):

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#include <SPI.h>
#include <Wire.h>
#include "driver/gpio.h"
#include "soc/gpio_periph.h"
#include "soc/io_mux_reg.h"
#include "soc/gpio_reg.h"
#include "driver/adc.h"

// Pins from mcu.kicad_sch
static constexpr int PIN_INHA = 33, PIN_INLA = 47;
static constexpr int PIN_INHB = 21, PIN_INLB = 18;
static constexpr int PIN_INHC = 17, PIN_INLC = 16;
static constexpr int PIN_DRV_CS = 12, PIN_DRV_SCLK = 13, PIN_DRV_SDI = 14, PIN_DRV_SDO = 15;
static constexpr int PIN_DRV_NSLEEP = 34, PIN_DRV_NFAULT = 48, PIN_DRV_DRVOFF = 35;
static constexpr int PIN_VM_SENSE = 7;
static constexpr int PIN_ISENSE[3] = {8, 9, 10};
static constexpr int PIN_ENC_SCL = 1, PIN_ENC_SDA = 2;

static constexpr int PIN_INH[3] = {PIN_INHA, PIN_INHB, PIN_INHC};
static constexpr int PIN_INL[3] = {PIN_INLA, PIN_INLB, PIN_INLC};

// DRV8316 registers
static constexpr uint8_t REG_IC_STATUS = 0x00, REG_STATUS1 = 0x01, REG_STATUS2 = 0x02;
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static void printDrvStatus() {
  uint8_t ic = drvRead(REG_IC_STATUS), s1 = drvRead(REG_STATUS1), s2 = drvRead(REG_STATUS2);
  Serial.printf("DRV8316: IC_STATUS=0x%02X STATUS1=0x%02X STATUS2=0x%02X CTRL1=0x%02X CTRL2=0x%02X nFAULT=%s\n", ic, s1,
                s2, drvRead(REG_CTRL1), drvRead(REG_CTRL2), digitalRead(PIN_DRV_NFAULT) ? "high(ok)" : "LOW(fault)");
  if (ic & 0x01) {
    Serial.print("  faults:");
    if (ic & 0x02) Serial.print(" OT");
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// ---------------- Measurements ----------------
static float readVm() {
  uint32_t mv = 0;
  for (int i = 0; i < 16; i++) mv += analogReadMilliVolts(PIN_VM_SENSE);
  return mv / 16.0f / 1000.0f * 11.0f;  // 100k / 10k divider
}

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}

static void disableDrive() {
  digitalWrite(PIN_DRV_DRVOFF, HIGH);
  for (int k = 0; k < 3; k++) {
    digitalWrite(PIN_INL[k], LOW);
    ledcWrite(k, 0);
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    Serial.println("ABORT: VM not in 8-16 V. Is the barrel jack plugged in?");
    return false;
  }
  digitalWrite(PIN_DRV_NSLEEP, HIGH);
  delay(5);
  drvWrite(REG_CTRL1, 0x03);  // unlock registers
  if ((drvRead(REG_CTRL1) & 0x07) != 0x03) {
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  // 3x mode: INHx = PWM, INLx = enable. Start with zero differential voltage.
  setVoltageVector(0, 0);
  for (int k = 0; k < 3; k++) digitalWrite(PIN_INL[k], HIGH);
  digitalWrite(PIN_DRV_DRVOFF, LOW);
  delay(2);
  // Zero-current offsets of the current sense amps (bridge active, zero differential voltage).
  readIsenseMv(isenseOffsetMv);
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                isenseOffsetMv[2]);
  enabled = true;
  printDrvStatus();
  if (!digitalRead(PIN_DRV_NFAULT)) {
    Serial.println("ABORT: nFAULT low after enable");
    disableDrive();
    return false;
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}

static bool faultCheck() {
  if (!digitalRead(PIN_DRV_NFAULT)) {
    disableDrive();
    Serial.println("FAULT: nFAULT went low, outputs disabled");
    printDrvStatus();
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  Serial.println("\n--- GPIO loopback (bridge Hi-Z) ---");
  disableDrive();
  Serial.printf("ledcSetup returned %u %u %u Hz\n", ledcSetupFreq[0], ledcSetupFreq[1], ledcSetupFreq[2]);
  const int pins[] = {PIN_INHA, PIN_INHB, PIN_INHC, PIN_INLA, PIN_INLB, PIN_INLC, PIN_DRV_DRVOFF, PIN_DRV_NSLEEP};
  for (int p : pins) PIN_INPUT_ENABLE(GPIO_PIN_MUX_REG[p]);

  const float duties[] = {0.0f, 0.25f, 0.5f, 0.75f};
  for (float d : duties) {
    for (int k = 0; k < 3; k++) ledcWrite(k, (uint32_t)(d * PWM_MAX));
    delay(5);
    Serial.printf("INH set %.2f -> measured A %.2f  B %.2f  C %.2f\n", d, highFraction(PIN_INHA), highFraction(PIN_INHB),
                  highFraction(PIN_INHC));
  }
  for (int k = 0; k < 3; k++) {
    ledcWrite(k, PWM_MAX / 2);
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    int l = gpio_get_level((gpio_num_t)PIN_INL[k]);
    Serial.printf("INL%c (IO%d): write 1 -> %d, write 0 -> %d\n", 'A' + k, PIN_INL[k], h, l);
  }
  digitalWrite(PIN_DRV_DRVOFF, LOW);
  delay(1);
  int l = gpio_get_level((gpio_num_t)PIN_DRV_DRVOFF);
  digitalWrite(PIN_DRV_DRVOFF, HIGH);
  delay(1);
  Serial.printf("DRVOFF (IO35): write 0 -> %d, write 1 -> %d\n", l, gpio_get_level((gpio_num_t)PIN_DRV_DRVOFF));
  Serial.printf("nSLEEP (IO34): currently written %d, reads %d\n", enabled, gpio_get_level((gpio_num_t)PIN_DRV_NSLEEP));
}

// ---------------- Current-sense (SOx) diagnostics ----------------
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static void senseDiag() {
  Serial.println("\n--- Current-sense diagnostic ---");
  disableDrive();
  digitalWrite(PIN_DRV_NSLEEP, LOW);
  delay(5);
  for (int k = 0; k < 3; k++) analogReadMilliVolts(PIN_ISENSE[k]);
  Serial.println("pin config:");
  for (int k = 0; k < 3; k++) printPinCfg(PIN_ISENSE[k]);
  kickTest("DRV asleep");

  digitalWrite(PIN_DRV_NSLEEP, HIGH);
  delay(5);
  Serial.printf("CTRL5 (CSA gain etc) = 0x%02X\n", drvRead(0x07));
  kickTest("DRV awake, bridge Hi-Z");
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}

static void runAll() {
  digitalWrite(PIN_DRV_NSLEEP, HIGH);  // wake so SPI status is valid
  delay(5);
  printStatus();
  if (phaseStepTest() && polePairSweep()) {
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
void setup() {
  // Driver asleep and outputs Hi-Z until a test is requested.
  pinMode(PIN_DRV_NSLEEP, OUTPUT);
  digitalWrite(PIN_DRV_NSLEEP, LOW);
  pinMode(PIN_DRV_DRVOFF, OUTPUT);
  digitalWrite(PIN_DRV_DRVOFF, HIGH);
  pinMode(PIN_DRV_NFAULT, INPUT);
  for (int k = 0; k < 3; k++) {
    pinMode(PIN_INL[k], OUTPUT);
    digitalWrite(PIN_INL[k], LOW);
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  }
  pinMode(PIN_DRV_CS, OUTPUT);
  digitalWrite(PIN_DRV_CS, HIGH);
  drvSpi.begin(PIN_DRV_SCLK, PIN_DRV_SDO, PIN_DRV_SDI, -1);
  analogReadResolution(12);

  Serial.begin(115200);
  Wire.begin(PIN_ENC_SDA, PIN_ENC_SCL, 400000);
  encUpdate();
  encAccum = 0;
  Serial.println("\nsmartknob_driver motor test ready. Commands: r s p n f b v x");
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    case 'r': runAll(); break;
    case 's':
      if (!enabled) {
        digitalWrite(PIN_DRV_NSLEEP, HIGH);
        delay(5);
      }
      printStatus();
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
